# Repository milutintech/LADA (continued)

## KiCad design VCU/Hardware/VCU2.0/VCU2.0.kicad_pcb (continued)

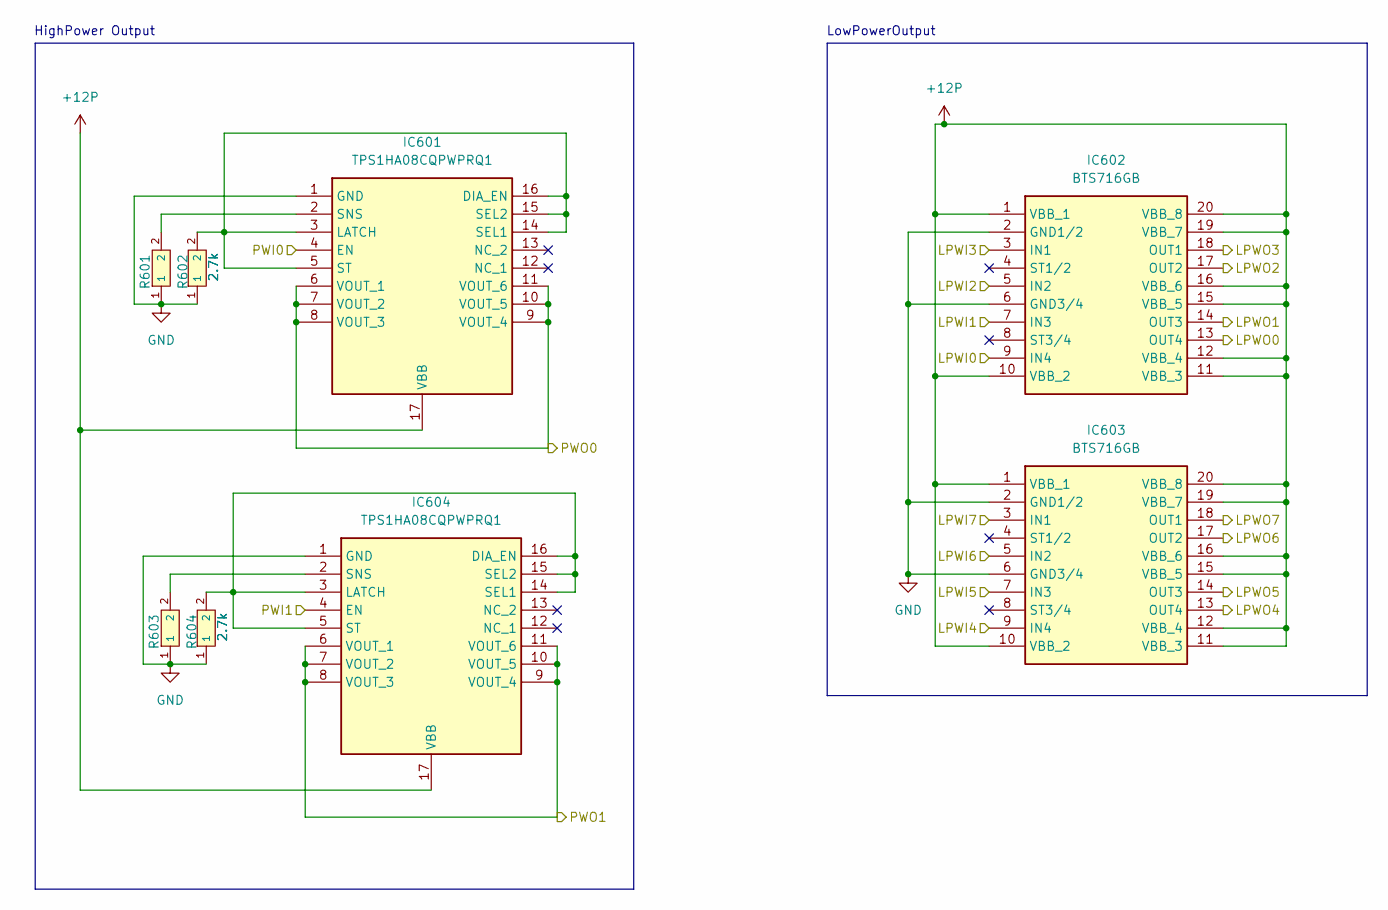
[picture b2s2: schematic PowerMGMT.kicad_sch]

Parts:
IC601, IC604: TPS1HA08CQPWPRQ1; SOP65P640X120-17N; Mouser Part Number 595-TPS1HA08DQPWPRQ1
IC602, IC603: BTS716GB; SOIC127P1030X265-20N; Mouser Part Number 726-BTS716GB
R601, R602, R603, R604: 2.7k; R0603; LCSC C3017728

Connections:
+12P: IC601.17 (VBB), IC602.1 (VBB_1), IC602.10 (VBB_2), IC602.11 (VBB_3), IC602.12 (VBB_4), IC602.15 (VBB_5), IC602.16 (VBB_6), IC602.19 (VBB_7), IC602.20 (VBB_8), IC603.1 (VBB_1), IC603.10 (VBB_2), IC603.11 (VBB_3), IC603.12 (VBB_4), IC603.15 (VBB_5), IC603.16 (VBB_6), IC603.19 (VBB_7), IC603.20 (VBB_8), IC604.17 (VBB); also elsewhere on the board
/Connector/LPWO0: IC602.13 (OUT4); also elsewhere on the board
/Connector/LPWO1: IC602.14 (OUT3); also elsewhere on the board
/Connector/LPWO2: IC602.17 (OUT2); also elsewhere on the board
/Connector/LPWO3: IC602.18 (OUT1); also elsewhere on the board
/Connector/LPWO4: IC603.13 (OUT4); also elsewhere on the board
/Connector/LPWO5: IC603.14 (OUT3); also elsewhere on the board
/Connector/LPWO6: IC603.17 (OUT2); also elsewhere on the board
/Connector/LPWO7: IC603.18 (OUT1); also elsewhere on the board
/Connector/PWO0: IC601.6 (VOUT_1), IC601.7 (VOUT_2), IC601.8 (VOUT_3), IC601.9 (VOUT_4), IC601.10 (VOUT_5), IC601.11 (VOUT_6); also elsewhere on the board
/Connector/PWO1: IC604.6 (VOUT_1), IC604.7 (VOUT_2), IC604.8 (VOUT_3), IC604.9 (VOUT_4), IC604.10 (VOUT_5), IC604.11 (VOUT_6); also elsewhere on the board
/PowerMGMT/LPWI0: IC602.9 (IN4); also elsewhere on the board
/PowerMGMT/LPWI1: IC602.7 (IN3); also elsewhere on the board
/PowerMGMT/LPWI2: IC602.5 (IN2); also elsewhere on the board
/PowerMGMT/LPWI3: IC602.3 (IN1); also elsewhere on the board
/PowerMGMT/LPWI4: IC603.9 (IN4); also elsewhere on the board
/PowerMGMT/LPWI5: IC603.7 (IN3); also elsewhere on the board
/PowerMGMT/LPWI6: IC603.5 (IN2); also elsewhere on the board
/PowerMGMT/LPWI7: IC603.3 (IN1); also elsewhere on the board
/PowerMGMT/PWI0: IC601.4 (EN); also elsewhere on the board
/PowerMGMT/PWI1: IC604.4 (EN); also elsewhere on the board
GND: IC601.1 (GND), IC602.2 (GND1/2), IC602.6 (GND3/4), IC603.2 (GND1/2), IC603.6 (GND3/4), IC604.1 (GND), R601.1, R602.1, R603.1, R604.1; also elsewhere on the board
unnamed: IC601.3 (LATCH), IC601.5 (ST), IC601.14 (SEL1), IC601.15 (SEL2), IC601.16 (DIA_EN), R602.2
unnamed: IC601.2 (SNS), R601.2
unnamed: IC604.3 (LATCH), IC604.5 (ST), IC604.14 (SEL1), IC604.15 (SEL2), IC604.16 (DIA_EN), R604.2
unnamed: IC604.2 (SNS), R603.2

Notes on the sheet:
HighPower Output
LowPowerOutput

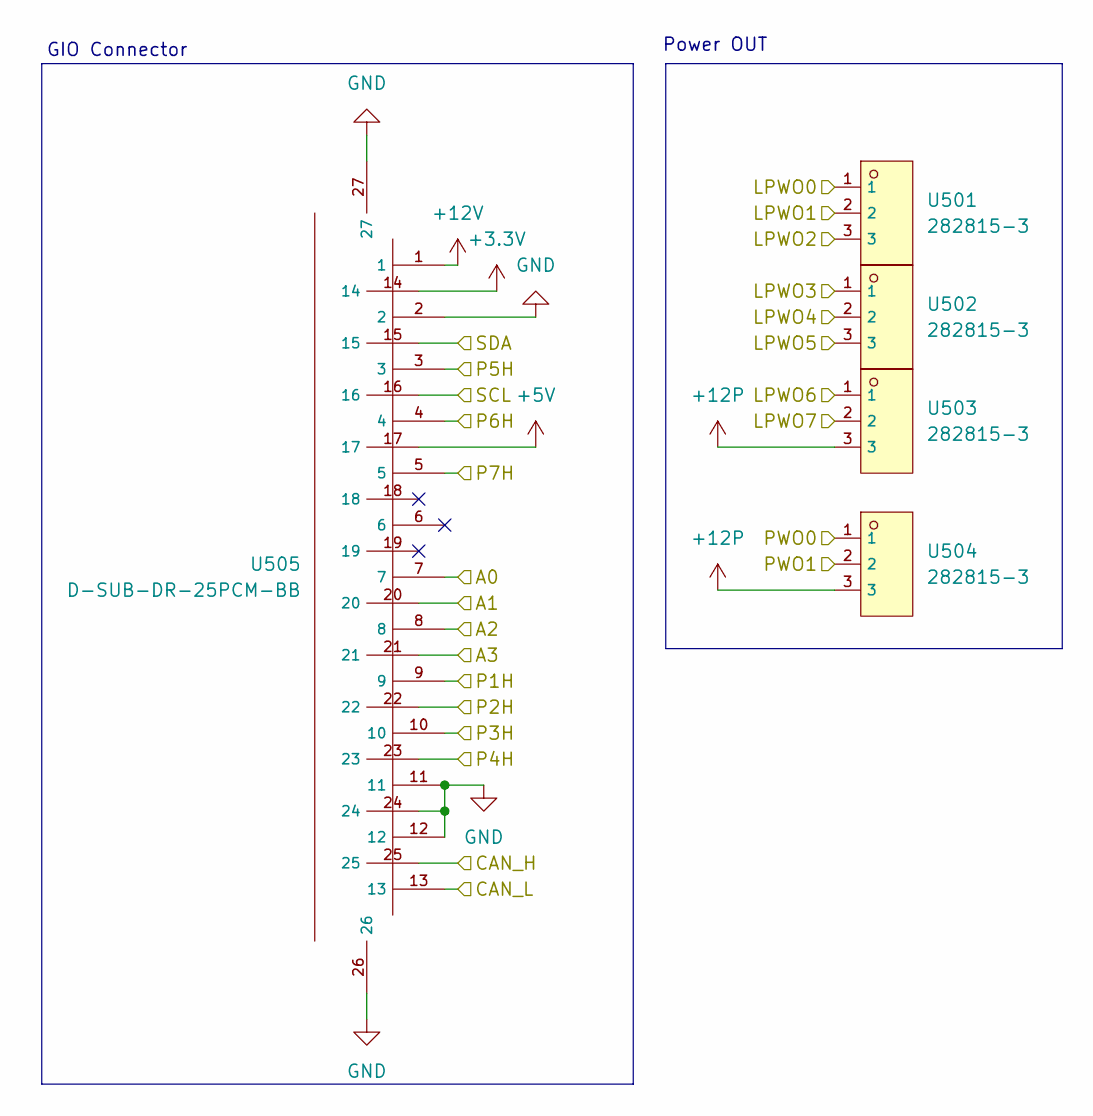
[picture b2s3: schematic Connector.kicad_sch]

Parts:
U501, U502, U503, U504: 282815-3; CONN-TH_3P-P5.08_TE_282815-3; LCSC C3009947
U505: D-SUB-DR-25PCM-BB; DB25-TH_D-SUB-DR-25PCM-BB; LCSC C19077339

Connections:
+3.3V: U505.14; also elsewhere on the board
+5V: U505.17; also elsewhere on the board
+12P: U503.3, U504.3; also elsewhere on the board
+12V: U505.1; also elsewhere on the board
/Connector/A0: U505.7; also elsewhere on the board
/Connector/A1: U505.20; also elsewhere on the board
/Connector/A2: U505.8; also elsewhere on the board
/Connector/A3: U505.21; also elsewhere on the board
/Connector/CAN_H: U505.25; also elsewhere on the board
/Connector/CAN_L: U505.13; also elsewhere on the board
/Connector/LPWO0: U501.1; also elsewhere on the board
/Connector/LPWO1: U501.2; also elsewhere on the board
/Connector/LPWO2: U501.3; also elsewhere on the board
/Connector/LPWO3: U502.1; also elsewhere on the board
/Connector/LPWO4: U502.2; also elsewhere on the board
/Connector/LPWO5: U502.3; also elsewhere on the board
/Connector/LPWO6: U503.1; also elsewhere on the board
/Connector/LPWO7: U503.2; also elsewhere on the board
/Connector/P1H: U505.9; also elsewhere on the board
/Connector/P2H: U505.22; also elsewhere on the board
/Connector/P3H: U505.10; also elsewhere on the board
/Connector/P4H: U505.23; also elsewhere on the board
/Connector/P5H: U505.3; also elsewhere on the board
/Connector/P6H: U505.4; also elsewhere on the board
/Connector/P7H: U505.5; also elsewhere on the board
/Connector/PWO0: U504.1; also elsewhere on the board
/Connector/PWO1: U504.2; also elsewhere on the board
/Connector/SCL: U505.16; also elsewhere on the board
/Connector/SDA: U505.15; also elsewhere on the board
GND: U505.2, U505.11, U505.12, U505.24, U505.26, U505.27; also elsewhere on the board

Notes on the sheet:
GIO Connector
Power OUT

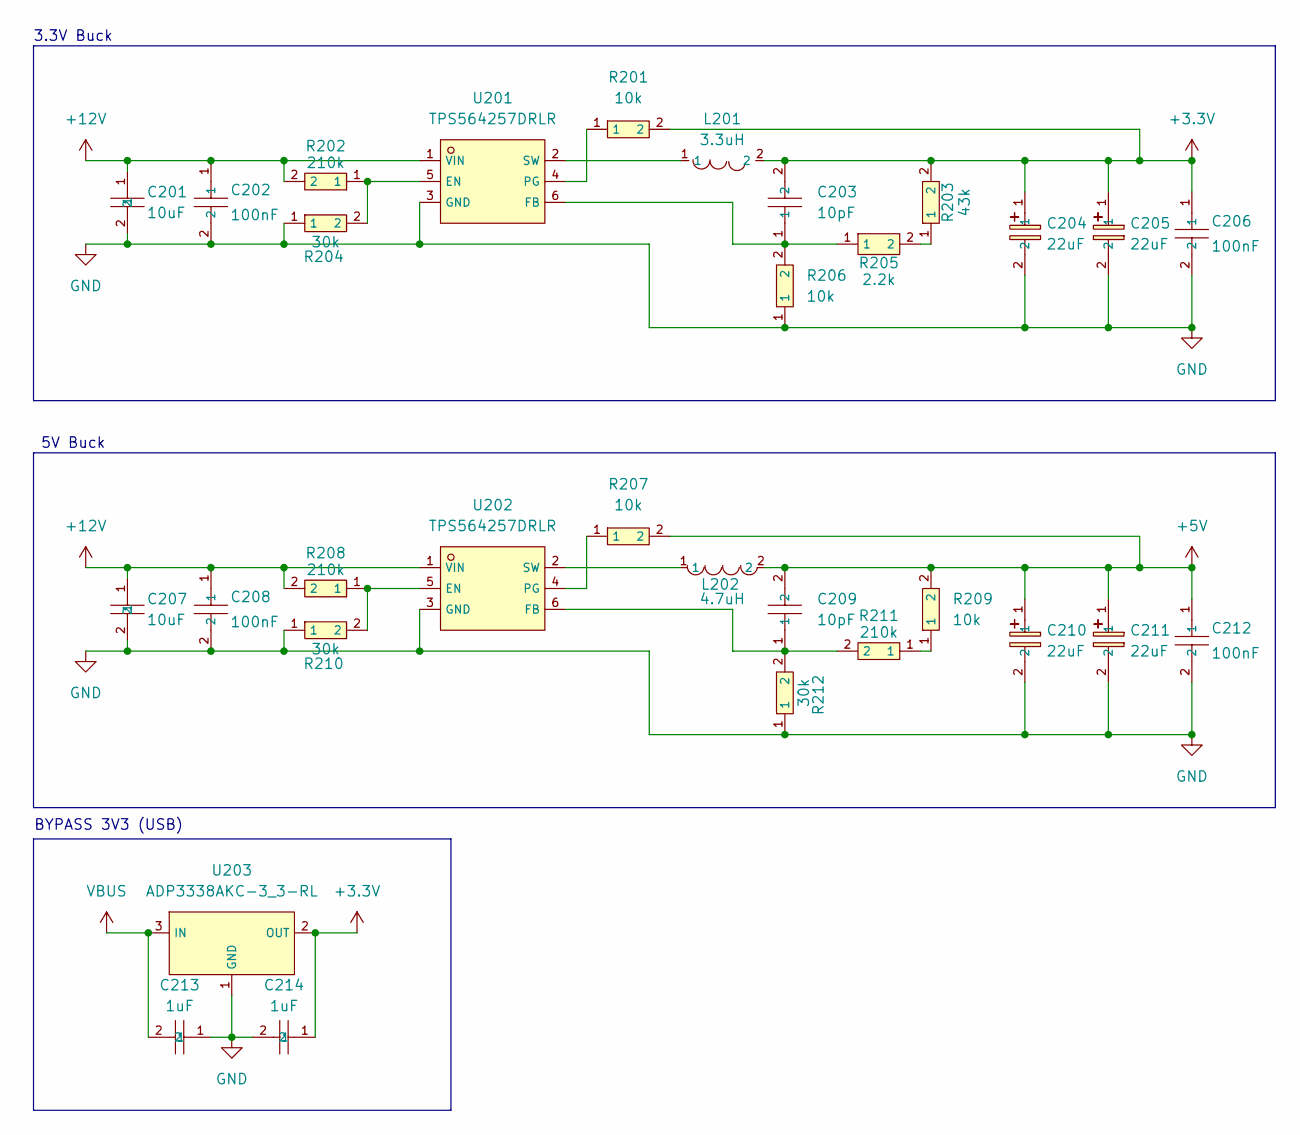
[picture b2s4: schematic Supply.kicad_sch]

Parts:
C201, C207: 10uF; C0805; LCSC C1713
C202, C206, C208, C212: 100nF; C0603; LCSC C14663
C203, C209: 10pF; C0603; LCSC C325468
C204, C205, C210, C211: 22uF; CAP-SMD_L7.3-W4.3-L-FD; LCSC C347543
C213, C214: 1uF; C0805; LCSC C28323
L201: 3.3uH; IND-SMD_L7.3-W6.6; LCSC C351116
L202: 4.7uH; IND-SMD_L3.3-W3.0; LCSC C285642
R201, R206, R207, R209: 10k; R0603; LCSC C98220
R202, R208, R211: 210k; R0603; LCSC C217875
R203: 43k; R0603; LCSC C137719
R204, R210, R212: 30k; R0603; LCSC C113302
R205: 2.2k; R0603; LCSC C227479
U201, U202: TPS564257DRLR; SOT-563-6_L1.6-W1.2-P0.5-LS1.6-BR; LCSC C19272233
U203: ADP3338AKC-3_3-RL; SOT-223-3_L6.5-W3.4-P2.30-LS7.0-BR-1; LCSC C3745342

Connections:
+3.3V: C203.2, C204.1, C205.1, C206.1, C214.1, L201.2, R201.2, R203.2, U203.2 (OUT); also elsewhere on the board
+5V: C209.2, C210.1, C211.1, C212.1, L202.2, R207.2, R209.2; also elsewhere on the board
+12V: C201.1, C202.1, C207.1, C208.1, R202.2, R208.2, U201.1 (VIN), U202.1 (VIN); also elsewhere on the board
GND: C201.2, C202.2, C204.2, C205.2, C206.2, C207.2, C208.2, C210.2, C211.2, C212.2, C213.1, C214.2, R204.1, R206.1, R210.1, R212.1, U201.3 (GND), U202.3 (GND), U203.1 (GND); also elsewhere on the board
unnamed: R203.1, R205.2
unnamed: R209.1, R211.1
unnamed: R202.1, R204.2, U201.5 (EN)
unnamed: C203.1, R205.1, R206.2, U201.6 (FB)
unnamed: R201.1, U201.4 (PG)
unnamed: L201.1, U201.2 (SW)
unnamed: R208.1, R210.2, U202.5 (EN)
unnamed: C209.1, R211.2, R212.2, U202.6 (FB)
unnamed: R207.1, U202.4 (PG)
unnamed: L202.1, U202.2 (SW)
VBUS: C213.2, U203.3 (IN); also elsewhere on the board

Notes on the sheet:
3.3V Buck
5V Buck
BYPASS 3V3 (USB)

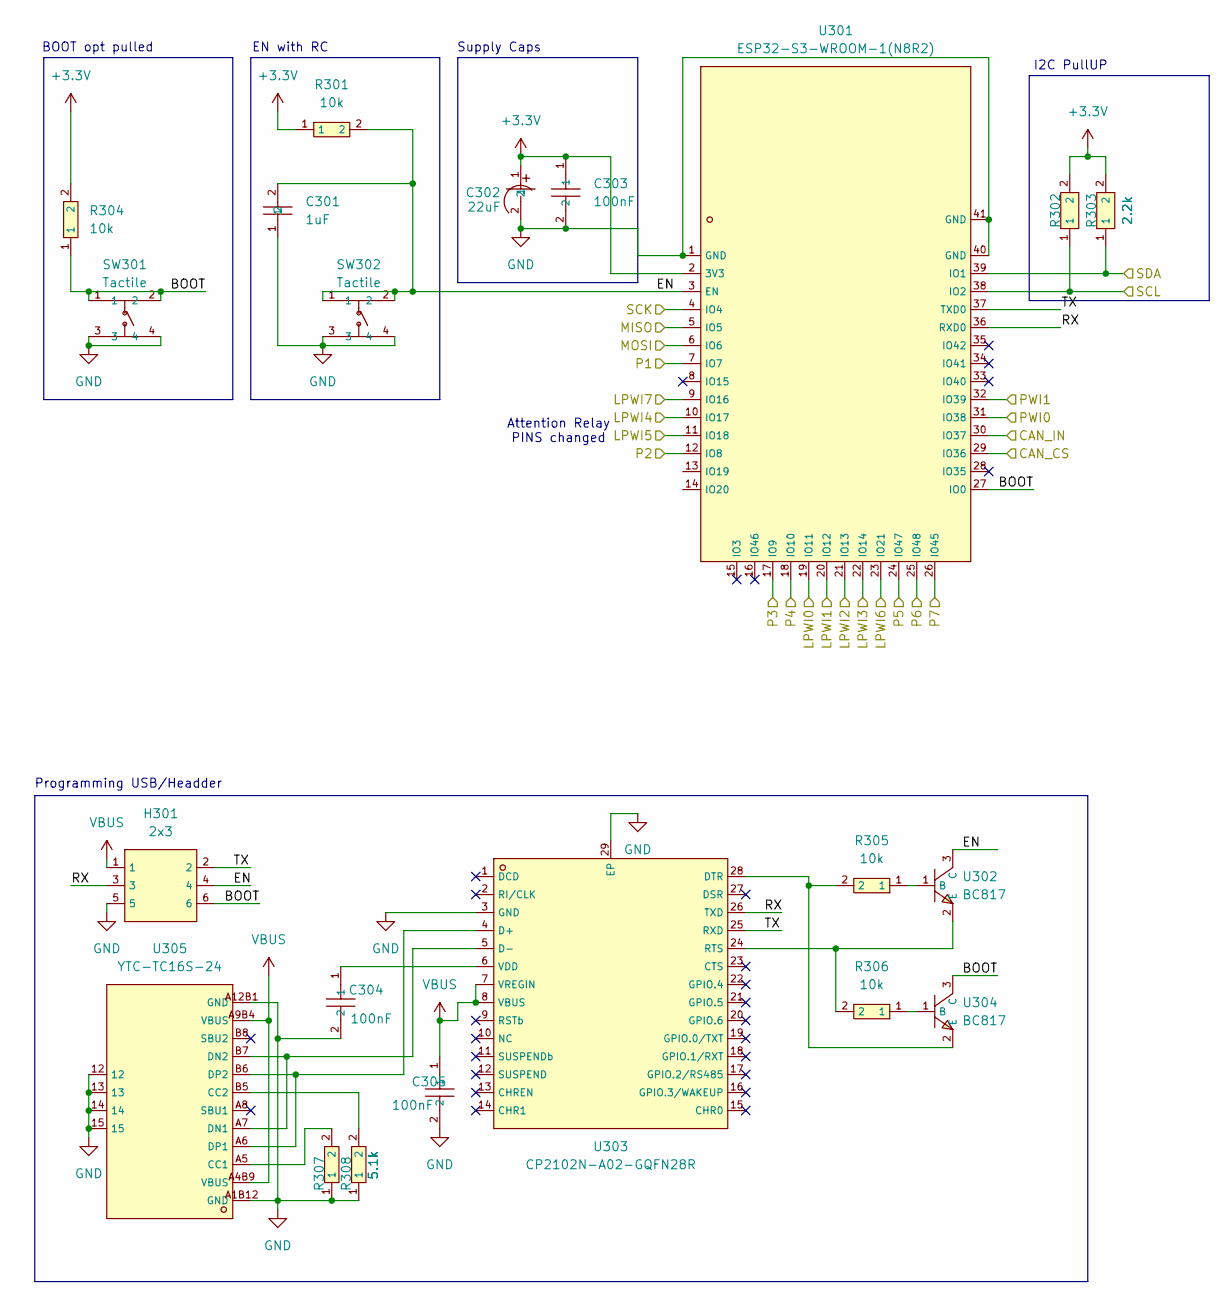
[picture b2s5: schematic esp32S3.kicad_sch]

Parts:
C301: 1uF; C0805; LCSC C28323
C302: 22uF; CAP-SMD_BD4.0-L4.3-W4.3-LS5.1-FD; LCSC C131114
C303, C304, C305: 100nF; C0603; LCSC C14663
H301: 2x3; HDR-TH_6P-P2.54-V-M-R2-C3-S2.54-1; LCSC C65114
R301, R304, R305, R306: 10k; R0603; LCSC C98220
R302, R303: 2.2k; R0603; LCSC C227479
R307, R308: 5.1k; R0603; LCSC C186203
SW301, SW302: Tactile; SW-SMD_4P-L6.0-W6.0-P4.50-LS9.0-2; LCSC C2837531
U301: ESP32-S3-WROOM-1(N8R2); WIRELM-SMD_ESP32-S3-WROOM-1; LCSC C2913204
U302, U304: BC817; SOT-23-3_L2.9-W1.3-P1.90-LS2.4-BR; LCSC C549442
U303: CP2102N-A02-GQFN28R; QFN-28_L5.0-W5.0-P0.50-TL-EP3.3; LCSC C964632
U305: YTC-TC16S-24; USB-C-SMD_YTC-TC16S-24; LCSC C2927291

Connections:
+3.3V: C302.1, C303.1, R301.1, R302.2, R303.2, R304.2, U301.2 (3V3); also elsewhere on the board
/Connector/SCL: R302.1, U301.38 (IO2); also elsewhere on the board
/Connector/SDA: R303.1, U301.39 (IO1); also elsewhere on the board
/IO/CAN_CS: U301.29 (IO36); also elsewhere on the board
/IO/CAN_IN: U301.30 (IO37); also elsewhere on the board
/IO/MISO: U301.5 (IO5); also elsewhere on the board
/IO/MOSI: U301.6 (IO6); also elsewhere on the board
/IO/P1: U301.7 (IO7); also elsewhere on the board
/IO/P2: U301.12 (IO8); also elsewhere on the board
/IO/P3: U301.17 (IO9); also elsewhere on the board
/IO/P4: U301.18 (IO10); also elsewhere on the board
/IO/P5: U301.24 (IO47); also elsewhere on the board
/IO/P6: U301.25 (IO48); also elsewhere on the board
/IO/P7: U301.26 (IO45); also elsewhere on the board
/IO/SCK: U301.4 (IO4); also elsewhere on the board
/PowerMGMT/LPWI0: U301.19 (IO11); also elsewhere on the board
/PowerMGMT/LPWI1: U301.20 (IO12); also elsewhere on the board
/PowerMGMT/LPWI2: U301.21 (IO13); also elsewhere on the board
/PowerMGMT/LPWI3: U301.22 (IO14); also elsewhere on the board
/PowerMGMT/LPWI4: U301.10 (IO17); also elsewhere on the board
/PowerMGMT/LPWI5: U301.11 (IO18); also elsewhere on the board
/PowerMGMT/LPWI6: U301.23 (IO21); also elsewhere on the board
/PowerMGMT/LPWI7: U301.9 (IO16); also elsewhere on the board
/PowerMGMT/PWI0: U301.31 (IO38); also elsewhere on the board
/PowerMGMT/PWI1: U301.32 (IO39); also elsewhere on the board
/esp32S3/BOOT: H301.6, R304.1, SW301.1, SW301.2, U301.27 (IO0), U304.3 (C)
/esp32S3/EN: C301.2, H301.4, R301.2, SW302.1, SW302.2, U301.3 (EN), U302.3 (C)
/esp32S3/RX: H301.3, U301.36 (RXD0), U303.26 (TXD)
/esp32S3/TX: H301.2, U301.37 (TXD0), U303.25 (RXD)
GND: C301.1, C302.2, C303.2, C304.2, C305.2, H301.5, R307.1, R308.1, SW301.3, SW301.4, SW302.3, SW302.4, U301.1 (GND), U301.40 (GND), U301.41 (GND), U303.3 (GND), U303.29 (EP), U305.12, U305.13, U305.14, U305.15, U305.A1B12 (GND), U305.A12B1 (GND); also elsewhere on the board
unnamed: R305.1, U302.1 (B)
unnamed: R306.2, U302.2 (E), U303.24 (RTS)
unnamed: U303.4 (D+), U305.A6 (DP1), U305.B6 (DP2)
unnamed: U303.5 (D-), U305.A7 (DN1), U305.B7 (DN2)
unnamed: R305.2, U303.28 (DTR), U304.2 (E)
unnamed: C304.1, U303.6 (VDD)
unnamed: R306.1, U304.1 (B)
unnamed: R307.2, U305.A5 (CC1)
unnamed: R308.2, U305.B5 (CC2)
VBUS: C305.1, H301.1, U303.7 (VREGIN), U303.8 (VBUS), U305.A4B9 (VBUS), U305.A9B4 (VBUS); also elsewhere on the board

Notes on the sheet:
EN with RC
Programming USB/Headder
I2C PullUP
Supply Caps
Attention Relay PINS changed
BOOT opt pulled

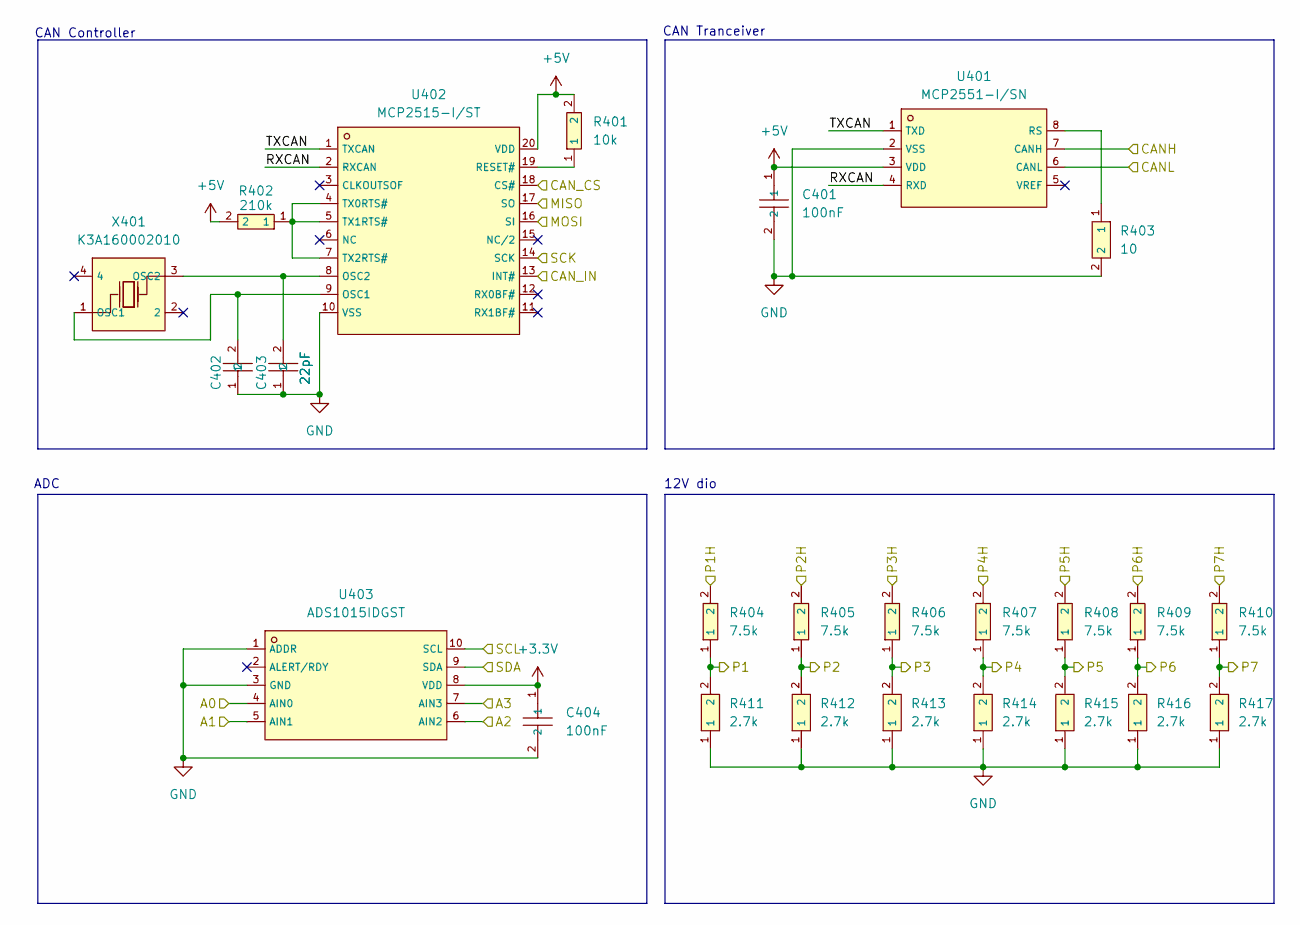
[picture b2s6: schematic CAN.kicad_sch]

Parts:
C401, C404: 100nF; C0603; LCSC C14663
C402, C403: 22pF; C0603; LCSC C105620
R401: 10k; R0603; LCSC C98220
R402: 210k; R0603; LCSC C217875
R403: 10; R0603; LCSC C403411
R404, R405, R406, R407, R408, R409, R410: 7.5k; R0603; LCSC C328377
R411, R412, R413, R414, R415, R416, R417: 2.7k; R0603; LCSC C3017728
U401: MCP2551-I/SN; SOIC-8_L4.9-W3.9-P1.27-LS6.0-BL; LCSC C7376
U402: MCP2515-I/ST; TSSOP-20_L6.5-W4.4-P0.65-LS6.4-BL; LCSC C15193
U403: ADS1015IDGST; VSSOP-10_L3.0-W3.0-P0.50-LS4.9-BL; LCSC C701606
X401: K3A160002010; CRYSTAL-SMD_4P-L3.2-W2.5-BL; LCSC C368736

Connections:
+3.3V: C404.1, U403.8 (VDD); also elsewhere on the board
+5V: C401.1, R401.2, R402.2, U401.3 (VDD), U402.20 (VDD); also elsewhere on the board
/Connector/A0: U403.4 (AIN0); also elsewhere on the board
/Connector/A1: U403.5 (AIN1); also elsewhere on the board
/Connector/A2: U403.6 (AIN2); also elsewhere on the board
/Connector/A3: U403.7 (AIN3); also elsewhere on the board
/Connector/CAN_H: U401.7 (CANH); also elsewhere on the board
/Connector/CAN_L: U401.6 (CANL); also elsewhere on the board
/Connector/P1H: R404.2; also elsewhere on the board
/Connector/P2H: R405.2; also elsewhere on the board
/Connector/P3H: R406.2; also elsewhere on the board
/Connector/P4H: R407.2; also elsewhere on the board
/Connector/P5H: R408.2; also elsewhere on the board
/Connector/P6H: R409.2; also elsewhere on the board
/Connector/P7H: R410.2; also elsewhere on the board
/Connector/SCL: U403.10 (SCL); also elsewhere on the board
/Connector/SDA: U403.9 (SDA); also elsewhere on the board
/IO/CAN_CS: U402.18 (CS#); also elsewhere on the board
/IO/CAN_IN: U402.13 (INT#); also elsewhere on the board
/IO/MISO: U402.17 (SO); also elsewhere on the board
/IO/MOSI: U402.16 (SI); also elsewhere on the board
/IO/P1: R404.1, R411.2; also elsewhere on the board
/IO/P2: R405.1, R412.2; also elsewhere on the board
/IO/P3: R406.1, R413.2; also elsewhere on the board
/IO/P4: R407.1, R414.2; also elsewhere on the board
/IO/P5: R408.1, R415.2; also elsewhere on the board
/IO/P6: R409.1, R416.2; also elsewhere on the board
/IO/P7: R410.1, R417.2; also elsewhere on the board
/IO/RXCAN: U401.4 (RXD), U402.2 (RXCAN)
/IO/SCK: U402.14 (SCK); also elsewhere on the board
/IO/TXCAN: U401.1 (TXD), U402.1 (TXCAN)
GND: C401.2, C402.1, C403.1, C404.2, R403.2, R411.1, R412.1, R413.1, R414.1, R415.1, R416.1, R417.1, U401.2 (VSS), U402.10 (VSS), U403.1 (ADDR), U403.3 (GND); also elsewhere on the board
unnamed: R403.1, U401.8 (RS)
unnamed: C402.2, U402.9 (OSC1), X401.1 (OSC1)
unnamed: C403.2, U402.8 (OSC2), X401.3 (OSC2)
unnamed: R401.1, U402.19 (RESET#)
unnamed: R402.1, U402.4 (TX0RTS#), U402.5 (TX1RTS#), U402.7 (TX2RTS#)

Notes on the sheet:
ADC
CAN Tranceiver
12V dio
CAN Controller

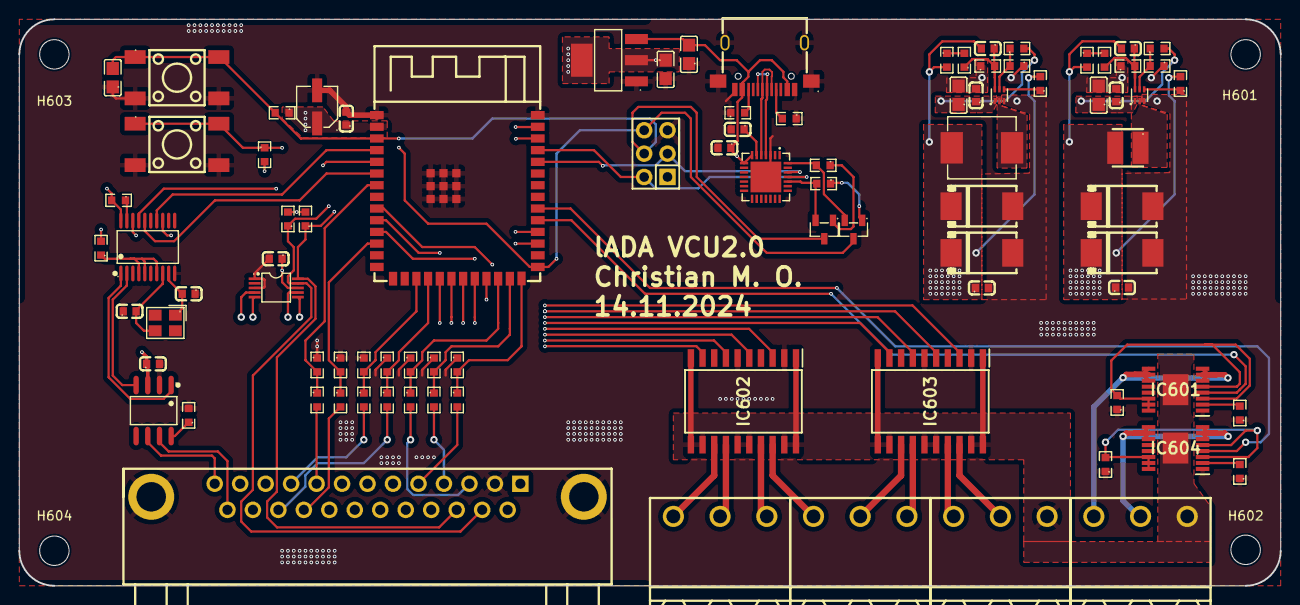
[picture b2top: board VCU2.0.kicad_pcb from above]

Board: 4 copper layers, 137.2 x 61.6 mm, 94 parts (0 on the bottom side), 87 nets.

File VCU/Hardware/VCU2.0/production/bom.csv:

Designator,Footprint,Quantity,Value,LCSC Part #
"C201, C207",C0805,2,10uF,C1713
"C202, C206, C208, C212, C303, C304, C305, C401, C404",C0603,9,100nF,C14663
"C203, C209",C0603,2,10pF,C325468
"C204, C205, C210, C211",CAP-SMD_L7.3-W4.3-L-FD,4,22uF,C347543
"C213, C214, C301",C0805,3,1uF,C28323
C302,CAP-SMD_BD4.0-L4.3-W4.3-LS5.1-FD,1,22uF,C131114
"C402, C403",C0603,2,22pF,C105620
H301,HDR-TH_6P-P2.54-V-M-R2-C3-S2.54-1,1,2x3,C65114
"IC601, IC604",SOP65P640X120-17N,2,TPS1HA08CQPWPRQ1,
"IC602, IC603",SOIC127P1030X265-20N,2,BTS716GB,
L201,IND-SMD_L7.3-W6.6,1,3.3uH,C351116
L202,IND-SMD_L3.3-W3.0,1,4.7uH,C285642
"R201, R206, R207, R209, R301, R304, R305, R306, R401",R0603,9,10k,C98220
"R202, R208, R211, R402",R0603,4,210k,C217875
R203,R0603,1,43k,C137719
"R204, R210, R212",R0603,3,30k,C113302
"R205, R302, R303",R0603,3,2.2k,C227479
"R307, R308",R0603,2,5.1k,C186203
R403,R0603,1,10,C403411
"R404, R405, R406, R407, R408, R409, R410",R0603,7,7.5k,C328377
"R411, R412, R413, R414, R415, R416, R417, R601, R602, R603, R604",R0603,11,2.7k,C3017728
"SW301, SW302",SW-SMD_4P-L6.0-W6.0-P4.50-LS9.0-2,2,Tactile,C2837531
"U201, U202",SOT-563-6_L1.6-W1.2-P0.5-LS1.6-BR,2,TPS564257DRLR,C19272233
U203,SOT-223-3_L6.5-W3.4-P2.30-LS7.0-BR-1,1,ADP3338AKC-3_3-RL,C3745342
U301,WIRELM-SMD_ESP32-S3-WROOM-1,1,ESP32-S3-WROOM-1(N8R2),C2913204
"U302, U304",SOT-23-3_L2.9-W1.3-P1.90-LS2.4-BR,2,BC817,C549442
U303,QFN-28_L5.0-W5.0-P0.50-TL-EP3.3,1,CP2102N-A02-GQFN28R,C964632
U305,USB-C-SMD_YTC-TC16S-24,1,YTC-TC16S-24,C2927291
U401,SOIC-8_L4.9-W3.9-P1.27-LS6.0-BL,1,MCP2551-I/SN,C7376
U402,TSSOP-20_L6.5-W4.4-P0.65-LS6.4-BL,1,MCP2515-I/ST,C15193
U403,VSSOP-10_L3.0-W3.0-P0.50-LS4.9-BL,1,ADS1015IDGST,C701606
"U501, U502, U503, U504",CONN-TH_3P-P5.08_TE_282815-3,4,282815-3,C3009947
U505,DB25-TH_D-SUB-DR-25PCM-BB,1,D-SUB-DR-25PCM-BB,C19077339
X401,CRYSTAL-SMD_4P-L3.2-W2.5-BL,1,K3A160002010,C368736

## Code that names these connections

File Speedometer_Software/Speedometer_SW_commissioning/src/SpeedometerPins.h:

#ifndef SPEEDOMETER_PINS_H
#define SPEEDOMETER_PINS_H

// Speedometer Pin Definitions
// Based on the ESP32 GPIO numbers (IO pins), not physical pin numbers

// NeoPixel Pin - Keep speedometer's original pin
#define NEOPIXEL_PIN 14  // IO14 for NeoPixel data pin

// CAN and SPI pins - Using IO numbers from the diagram
#define SPI_SCK_PIN 4     // IO4 for SCK
#define SPI_MISO_PIN 5    // IO5 for MISO
#define SPI_MOSI_PIN 6    // IO6 for MOSI
#define CAN_CS_PIN 7      // IO7 for CS
#define CAN_INT_PIN 12    // IO12 for INT (shown as 12 in the diagram)

// I2C Bus 1 pins - Total KM and Trip KM displays
#define I2C_SDA_PIN 1     // IO1 for SDA
#define I2C_SCL_PIN 2     // IO2 for SCL

// I2C Bus 2 pins - Speed and Drive Mode displays
#define I2C2_SDA_PIN 19   // IO19 for SDA_2
#define I2C2_SCL_PIN 20   // IO20 for SCL_2

#endif // SPEEDOMETER_PINS_H

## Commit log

2023-11-07 New Project
2023-11-07 Portng from Arudino
2023-11-07 Added NLGcomm
2023-11-07 Added DMC Com
2023-11-07 Added BSC Com
2023-11-07 Added Description
2023-11-08 Addes Comments to VCU main and added workspace
2023-11-09 Update functions.cpp with ADAC code
2023-11-09 general file update
2023-11-09 Added sampler to Main
2023-11-09 changed sampler added comments
2023-11-09 Remove Probably unused typedef
2023-11-09 Updatet run states
2023-11-09 read me
2023-11-10 Fixing Bugs with ADAC
2023-11-10 Changed bnoard type
2023-11-10 added baud rate modifier
2023-11-10 It fucking works
2023-11-16 dont know if i did something right
2023-11-16 did some shit
2023-11-16 Added deep sleep
2023-11-16 try to read internal ADC
2023-11-17 fuckin adc bug still persists
2023-11-28 binary
2023-12-05 Addes arming system with precharge
    Added all arming systems and laied ground for BMS current limiting
2023-12-07 Coments added
2023-12-08 fucking precharge
2024-01-12 ADD: Altium Project
2024-01-14 changed folder struct
2024-01-14 added file
2024-01-14 Added KiCad files
2024-01-16 Added altium Project complete scematics
2024-01-16 Layout
2024-01-18 continued
2024-01-18 advancements
2024-01-18 done
2024-01-20 update for VCU HW
2024-01-20 removed LCD and AD
2024-01-20 Added new ADC
2024-01-20 started display
2024-01-23 nextion screen
2024-01-27 some updates
2024-03-06 ADD Speedometer project
2024-03-06 First step Infotainment
2024-03-08 pocess
2024-03-08 First Mockup
2024-05-16 continued issue with can
2024-05-28 make different pages
2024-05-29 prepare charging page
    variable storage and can missing
2024-05-29 Add Tork and onroad / ofroad selector
2024-05-29 Version without password for valet mode
2024-07-18 remove streamlit buttons and add canhandler
2024-07-18 Move Modules in seperate folders
2024-07-18 Update LADAsys.py
    import lada Infotainment libs
2024-07-29 create schematics
2024-07-29 Create all Project schematics
2024-07-29 ADD ESP32s3
2024-07-29 ADD CAN and 7segment displays
2024-07-31 Start Speedometer Board outline
2024-08-01 Split Project to two PCB
2024-08-02 split altium project to faceplate and tech
2024-08-05 ADD Temp and Soc
2024-08-07 Placed Temp, SOC, Distance and Signal Neopixel
2024-08-08 ADD Placeholder for Lada Niva Logo
2024-08-08 ADD Alphanummerical Display
2024-08-08 ADD signal input and can
2024-08-20 ADD MAX6955 to project
2024-08-26 place torq leds
2024-08-27 ADD Supply for Neopixel
2024-09-03 Speedometer Add connectors on backside
2024-09-05 addedd trq mapp with offsetting for non 0-100pot
2024-09-05 added dmc files for oversight
2024-09-09 Edit can Layout
2024-09-10 Fixxed known bug
2024-09-11 Added timing sys for can msg send
    Dont hate the players hate the game
2024-09-11 OCHHCHHCHCH
    Hate Github its the bad game
2024-09-11 NLG shinanigans
2024-09-12 WHYYY WHYY
2024-09-12 space created for new ideas
2024-09-12 recive from info implemented
2024-09-12 No need for testing proffesional work
    should compile maybe(written in word)
2024-09-12 continue layout and schematic
2024-09-17 Routing Signalinput done
2024-09-17 start routing of signals
2024-09-27 ADD segment Displays Driver ic
2024-09-30 7seg ics
2024-10-03 ADD datasheet for leds and powercalc
2024-10-21 Modify Schematic, start Layout DCDC
2024-10-21 Update main.cpp
    test implement for delay on connection and diffrent aproach to unlocking
2024-10-21 Update main.cpp
    Added hysteresis to coling sys
2024-10-22 start Layout of DCDC
2024-10-24 Add current version of layout
2024-10-24 create kicad project
2024-10-26 adjusted precharge
2024-10-27 fixxed the charger unlock
2024-10-28 final before gpt revamp with throttle calib
2024-10-28 gbt go brr
2024-10-31 mimimi
2024-10-31 changes th bsc
2024-10-31 updatet can com with ma homie GPT
2024-10-31 precharge worki hopy hopy
2024-11-02 its running
2024-11-03 cahrging
2024-11-03 working
2024-11-04 finish layout of dcdc
2024-11-07 worki
2024-11-08 not qite okay
2024-11-08 mimi
2024-11-08 maybe
2024-11-08 Layout 7Seg nearly done
2024-11-09 Requ working more or less
2024-11-09 no opd
2024-11-09 now with more braincells used (actually compileing)
2024-11-09 added opd acording to paper if it woks maybe
2024-11-09 atleast requ is okay
2024-11-18 Layout preatty much done
    Button and poligones missing
2024-11-18 Change Altium to Rule
2024-11-18 Layout probably done?
2024-11-19 add holes to pcb
2024-11-24 try to upload kicad layout
2024-11-24 update kicad pcb
2024-11-25 VCU2.0
2024-11-27 Changed to VCU2.0 setup
2024-11-27 Added Test SW for VCU
2024-11-27 Create VCU.code-workspace
2024-11-27 updatet
2024-11-27 new val for pot
2024-11-28 seems god
2024-11-28 sub division
2024-11-28 compileing
2024-11-28 serial added no claude ai was used (water usage = insane)
2024-11-29 claude and i are besties
2024-11-30 okay danm debbuging?!
2024-12-01 okay
2024-12-02 updatet the init
2024-12-02 dual power
2024-12-02 some changes idk
2024-12-02 adjustet for idk
2024-12-02 adjust cann trimm
2024-12-16 neopixel test
2024-12-23 TLC debug
2024-12-24 dev stuff
2024-12-25 14segment seems ok
2024-12-25 some stuff working now
2024-12-25 working demo mode
2024-12-29 maybe working can utility for speedometer
2025-05-09 demo mode
2025-05-10 add fusion file and current step
2025-05-12 we got speeddo
2025-06-21 worki maybe¨
2025-08-09 Changed folder structure for RevA / RevB
2025-09-14 Changed handeling
2025-09-21 updated troq display with new neopixel
2025-11-11 current version of lada speedometer in kicad
2025-12-03 Speedometer DRC mostly passed
2025-12-04 maybe done?
2025-12-05 pcb should be done now
2025-12-07 Final Version, has been ordered
2026-05-16 16.05.2026
